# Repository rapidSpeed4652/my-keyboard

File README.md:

# my-keyboard
My repo for my keyboard!

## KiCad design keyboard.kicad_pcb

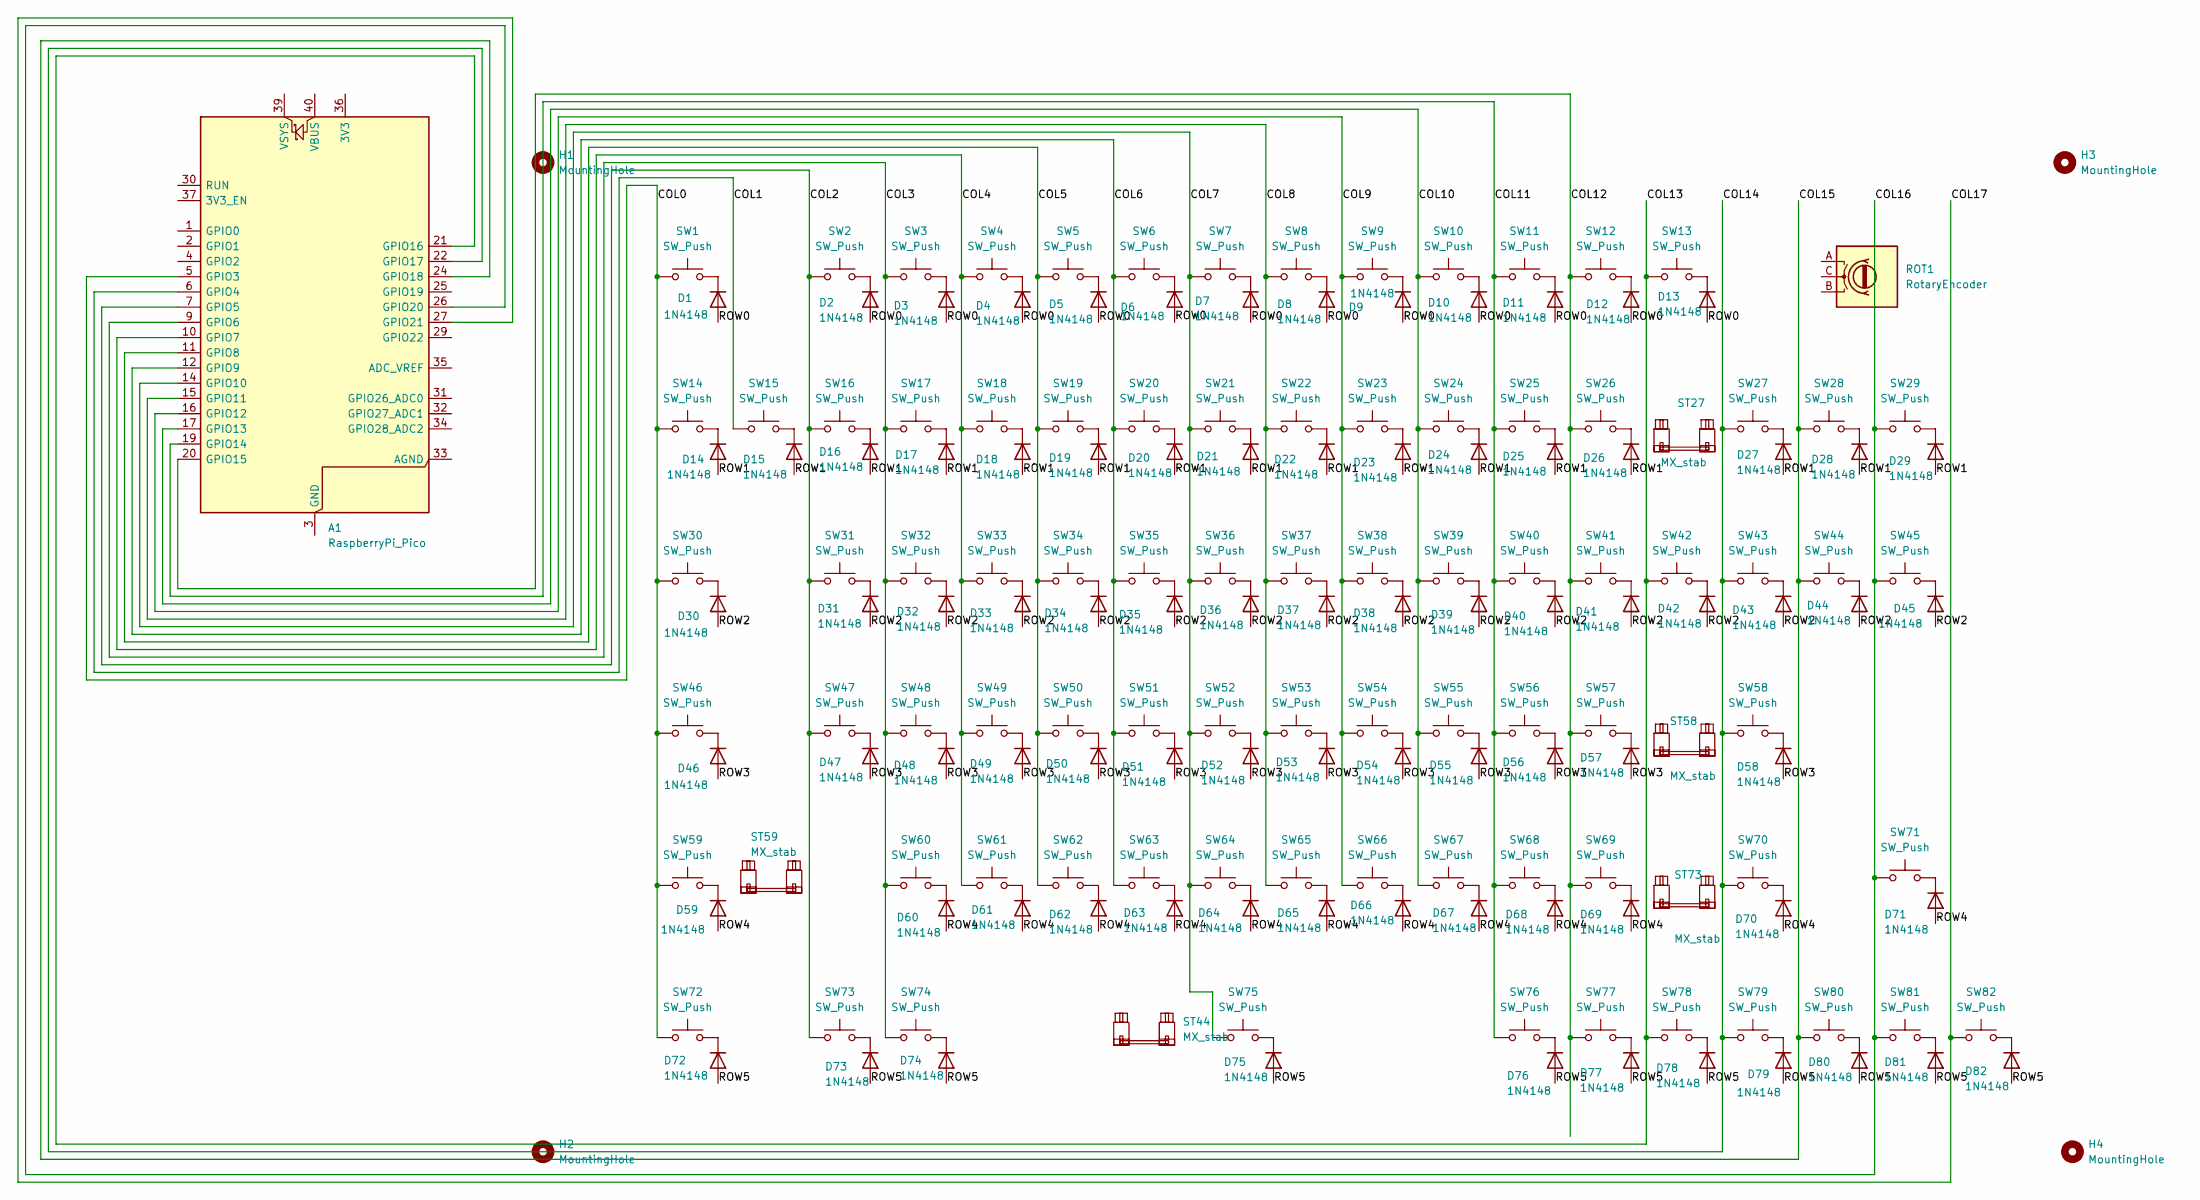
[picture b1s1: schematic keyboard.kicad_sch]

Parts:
A1: RaspberryPi_Pico; RaspberryPi_Pico_Common_THT
D1, D2, D3, D4, D5, D6, D7, D8, D9, D10, D11, D12, D13, D14, D15, D16, D17, D18, D19, D20, D21, D22, D23, D24, D25, D26, D27, D28, D29, D30, D31, D32, D33, D34, D35, D36, D37, D38, D39, D40, D41, D42, D43, D44, D45, D46, D47, D48, D49, D50, D51, D52, D53, D54, D55, D56, D57, D58, D59, D60, D61, D62, D63, D64, D65, D66, D67, D68, D69, D70, D71, D72, D73, D74, D75, D76, D77, D78, D79, D80, D81, D82: 1N4148; D_DO-35_SOD27_P7.62mm_Horizontal
H1, H2, H3, H4: MountingHole; MountingHole_2.1mm
ROT1: RotaryEncoder; RotaryEncoder_Alps_EC11E_Vertical_H20mm
ST27: MX_stab; STAB_MX_P_2u
ST44: MX_stab; STAB_MX_P_6.25u
ST58, ST59: MX_stab; STAB_MX_P_2.25u
ST73: MX_stab; STAB_MX_P_2.75u
SW1, SW2, SW3, SW4, SW5, SW6, SW7, SW8, SW9, SW10, SW11, SW12, SW13, SW14, SW15, SW16, SW17, SW18, SW19, SW20, SW21, SW22, SW23, SW24, SW25, SW26, SW27, SW28, SW29, SW30, SW31, SW32, SW33, SW34, SW35, SW36, SW37, SW38, SW39, SW40, SW41, SW42, SW43, SW44, SW45, SW46, SW47, SW48, SW49, SW50, SW51, SW52, SW53, SW54, SW55, SW56, SW57, SW58, SW59, SW60, SW61, SW62, SW63, SW64, SW65, SW66, SW67, SW68, SW69, SW70, SW71, SW72, SW73, SW74, SW75, SW76, SW77, SW78, SW79, SW80, SW81, SW82: SW_Push; SW_MX_1u

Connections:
/COL0: A1.5 (GPIO3), SW1.1, SW14.1, SW30.1, SW46.1, SW59.1, SW72.1
/COL1: A1.6 (GPIO4), SW15.1
/COL2: A1.7 (GPIO5), SW2.1, SW16.1, SW31.1, SW47.1, SW73.1
/COL3: A1.9 (GPIO6), SW3.1, SW17.1, SW32.1, SW48.1, SW60.1, SW74.1
/COL4: A1.10 (GPIO7), SW4.1, SW18.1, SW33.1, SW49.1, SW61.1
/COL5: A1.11 (GPIO8), SW5.1, SW19.1, SW34.1, SW50.1, SW62.1
/COL6: A1.12 (GPIO9), SW6.1, SW20.1, SW35.1, SW51.1, SW63.1
/COL7: A1.14 (GPIO10), SW7.1, SW21.1, SW36.1, SW52.1, SW64.1, SW75.1
/COL8: A1.15 (GPIO11), SW8.1, SW22.1, SW37.1, SW53.1, SW65.1
/COL9: A1.16 (GPIO12), SW9.1, SW23.1, SW38.1, SW54.1, SW66.1
/COL10: A1.17 (GPIO13), SW10.1, SW24.1, SW39.1, SW55.1, SW67.1
/COL11: A1.19 (GPIO14), SW11.1, SW25.1, SW40.1, SW56.1, SW68.1, SW76.1
/COL12: A1.20 (GPIO15), SW12.1, SW26.1, SW41.1, SW57.1, SW69.1, SW77.1
/COL13: A1.21 (GPIO16), SW13.1, SW42.1, SW78.1
/COL14: A1.22 (GPIO17), SW27.1, SW43.1, SW58.1, SW70.1, SW79.1
/COL15: A1.24 (GPIO18), SW28.1, SW44.1, SW80.1
/COL16: A1.26 (GPIO20), SW29.1, SW45.1, SW71.1, SW81.1
/COL17: A1.27 (GPIO21), SW82.1
/ROW0: D1.2 (A), D2.2 (A), D3.2 (A), D4.2 (A), D5.2 (A), D7.2 (A), D8.2 (A), D9.2 (A), D10.2 (A), D11.2 (A), D12.2 (A), D13.2 (A)
/ROW1: D14.2 (A), D15.2 (A), D16.2 (A), D17.2 (A), D18.2 (A), D19.2 (A), D20.2 (A), D21.2 (A), D22.2 (A), D23.2 (A), D24.2 (A), D25.2 (A), D26.2 (A), D27.2 (A), D28.2 (A), D29.2 (A)
/ROW2: D30.2 (A), D31.2 (A), D32.2 (A), D33.2 (A), D35.2 (A), D36.2 (A), D37.2 (A), D38.2 (A), D39.2 (A), D40.2 (A), D41.2 (A), D42.2 (A), D43.2 (A), D44.2 (A), D45.2 (A)
/ROW3: D46.2 (A), D47.2 (A), D48.2 (A), D49.2 (A), D50.2 (A), D51.2 (A), D52.2 (A), D53.2 (A), D54.2 (A), D55.2 (A), D56.2 (A), D57.2 (A), D58.2 (A)
/ROW4: D59.2 (A), D60.2 (A), D61.2 (A), D62.2 (A), D63.2 (A), D64.2 (A), D65.2 (A), D66.2 (A), D67.2 (A), D68.2 (A), D69.2 (A), D70.2 (A), D71.2 (A)
/ROW5: D72.2 (A), D73.2 (A), D74.2 (A), D75.2 (A), D76.2 (A), D77.2 (A), D78.2 (A), D79.2 (A), D80.2 (A), D81.2 (A), D82.2 (A)
unnamed: A1.3 (GND), A1.8 (GND), A1.13 (GND), A1.18 (GND), A1.23 (GND), A1.28 (GND), A1.38 (GND)
unnamed: D1.1 (K), SW1.2
unnamed: D2.1 (K), SW2.2
unnamed: D3.1 (K), SW3.2
unnamed: D4.1 (K), SW4.2
unnamed: D5.1 (K), SW5.2
unnamed: D6.1 (K_1), SW6.2
unnamed: D7.1 (K), SW7.2
unnamed: D8.1 (K), SW8.2
unnamed: D9.1 (K), SW9.2
unnamed: D10.1 (K), SW10.2
unnamed: D11.1 (K), SW11.2
unnamed: D12.1 (K), SW12.2
unnamed: D13.1 (K), SW13.2
unnamed: D14.1 (K), SW14.2
unnamed: D15.1 (K), SW15.2
unnamed: D16.1 (K), SW16.2
unnamed: D17.1 (K), SW17.2
unnamed: D18.1 (K), SW18.2
unnamed: D19.1 (K), SW19.2
unnamed: D20.1 (K), SW20.2
unnamed: D21.1 (K), SW21.2
unnamed: D22.1 (K), SW22.2
unnamed: D23.1 (K), SW23.2
unnamed: D24.1 (K), SW24.2
unnamed: D25.1 (K), SW25.2
unnamed: D26.1 (K), SW26.2
unnamed: D27.1 (K), SW27.2
unnamed: D28.1 (K), SW28.2
unnamed: D29.1 (K), SW29.2
unnamed: D30.1 (K), SW30.2
unnamed: D31.1 (K), SW31.2
unnamed: D32.1 (K), SW32.2
unnamed: D33.1 (K), SW33.2
unnamed: D34.1 (K_1), SW34.2
unnamed: D35.1 (K), SW35.2
unnamed: D36.1 (K), SW36.2
unnamed: D37.1 (K), SW37.2
unnamed: D38.1 (K), SW38.2
unnamed: D39.1 (K), SW39.2
unnamed: D40.1 (K), SW40.2
unnamed: D41.1 (K), SW41.2
unnamed: D42.1 (K), SW42.2
unnamed: D43.1 (K), SW43.2
unnamed: D44.1 (K), SW44.2
unnamed: D45.1 (K), SW45.2
unnamed: D46.1 (K), SW46.2
unnamed: D47.1 (K), SW47.2
unnamed: D48.1 (K), SW48.2
unnamed: D49.1 (K), SW49.2
unnamed: D50.1 (K), SW50.2
unnamed: D51.1 (K), SW51.2
unnamed: D52.1 (K), SW52.2
unnamed: D53.1 (K), SW53.2
unnamed: D54.1 (K), SW54.2
unnamed: D55.1 (K), SW55.2
unnamed: D56.1 (K), SW56.2
unnamed: D57.1 (K), SW57.2
unnamed: D58.1 (K), SW58.2
unnamed: D59.1 (K), SW59.2
unnamed: D60.1 (K), SW60.2
unnamed: D61.1 (K), SW61.2
unnamed: D62.1 (K), SW62.2
unnamed: D63.1 (K), SW63.2
unnamed: D64.1 (K), SW64.2
unnamed: D65.1 (K), SW65.2
unnamed: D66.1 (K), SW66.2
unnamed: D67.1 (K), SW67.2
unnamed: D68.1 (K), SW68.2
unnamed: D69.1 (K), SW69.2
unnamed: D70.1 (K), SW70.2
unnamed: D71.1 (K), SW71.2
unnamed: D72.1 (K), SW72.2
unnamed: D73.1 (K), SW73.2
unnamed: D74.1 (K), SW74.2
unnamed: D75.1 (K), SW75.2
unnamed: D76.1 (K), SW76.2
unnamed: D77.1 (K), SW77.2
unnamed: D78.1 (K), SW78.2
unnamed: D79.1 (K), SW79.2
unnamed: D80.1 (K), SW80.2
unnamed: D81.1 (K), SW81.2
unnamed: D82.1 (K), SW82.2

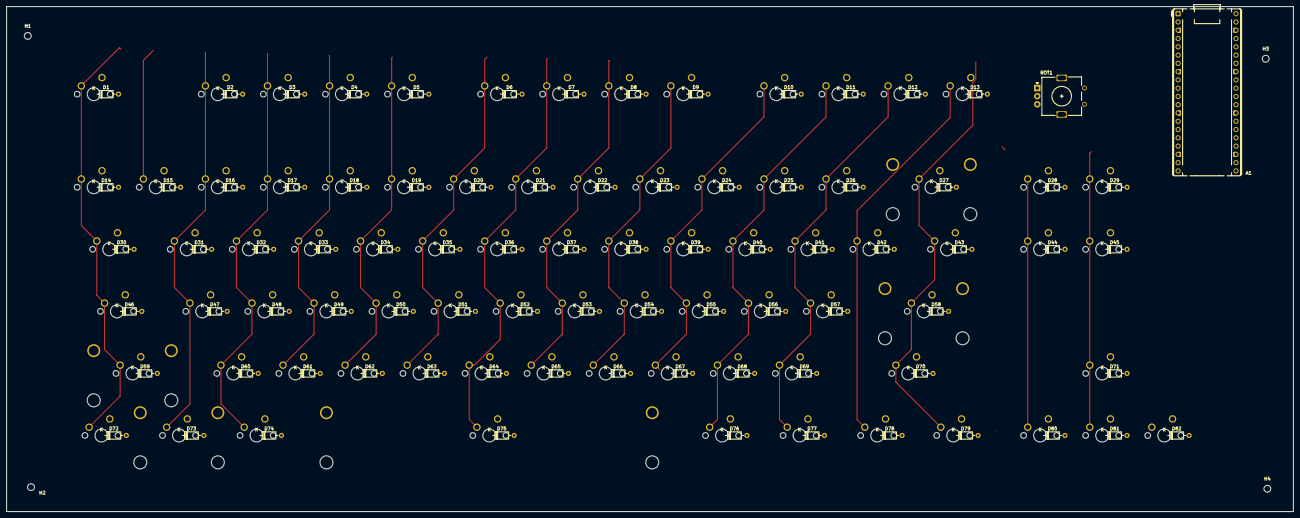
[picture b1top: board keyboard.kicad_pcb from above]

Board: 2 copper layers, 395.0 x 155.0 mm, 175 parts (0 on the bottom side), 107 nets.
